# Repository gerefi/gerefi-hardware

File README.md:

# gerefi-hardware

New repo just for gerefi Hardware

See also https://github.com/gerefi/gerefi/tree/master/hardware

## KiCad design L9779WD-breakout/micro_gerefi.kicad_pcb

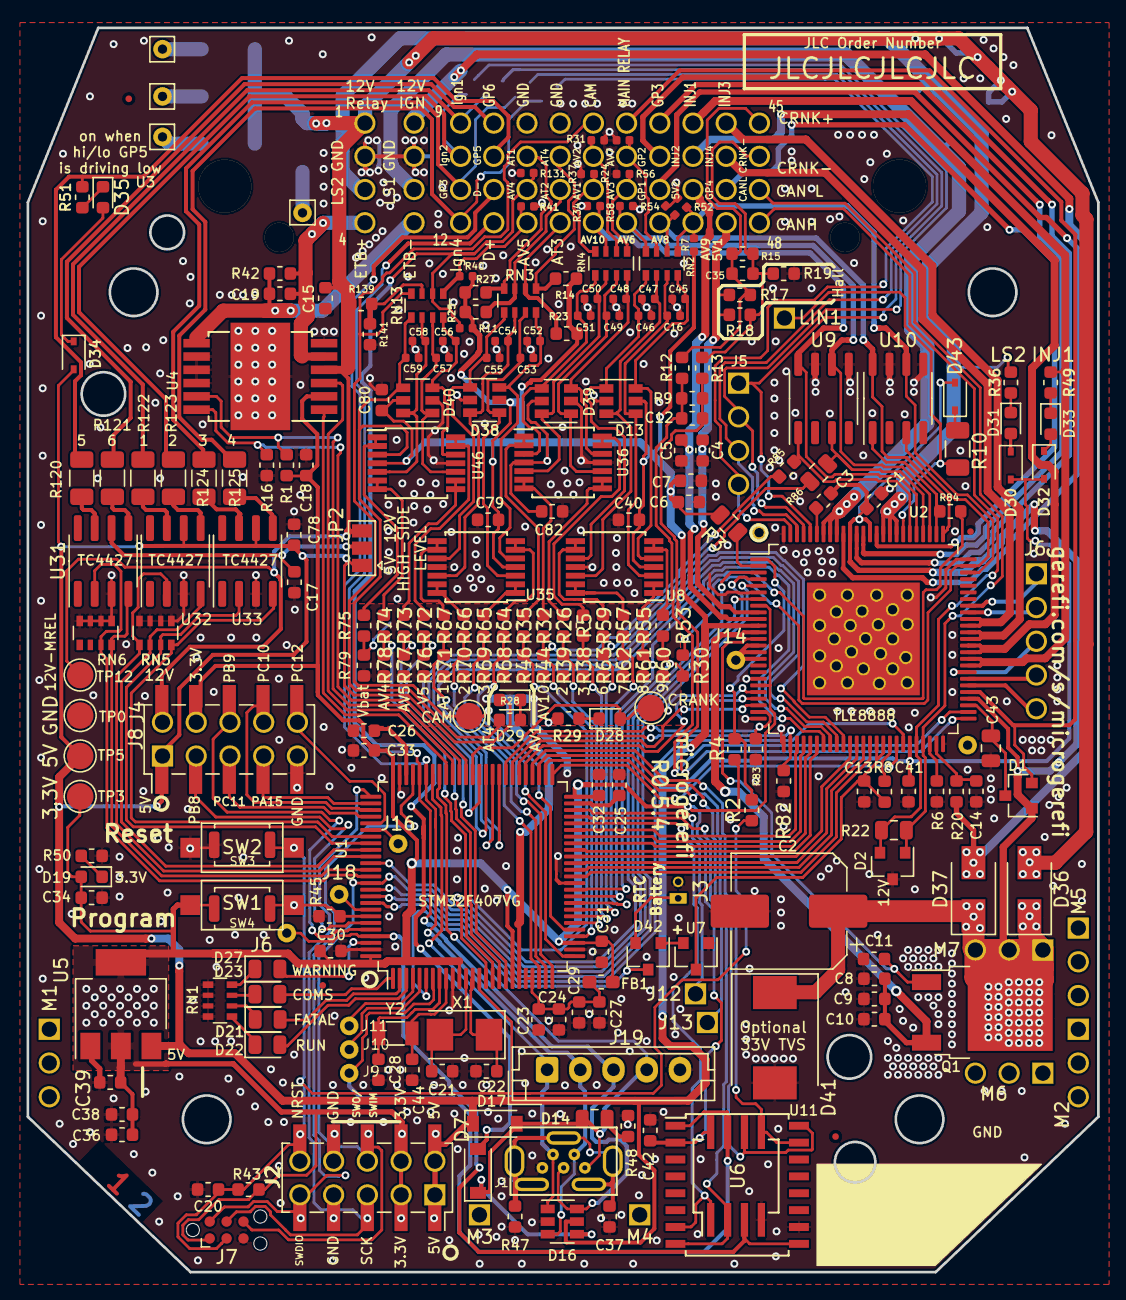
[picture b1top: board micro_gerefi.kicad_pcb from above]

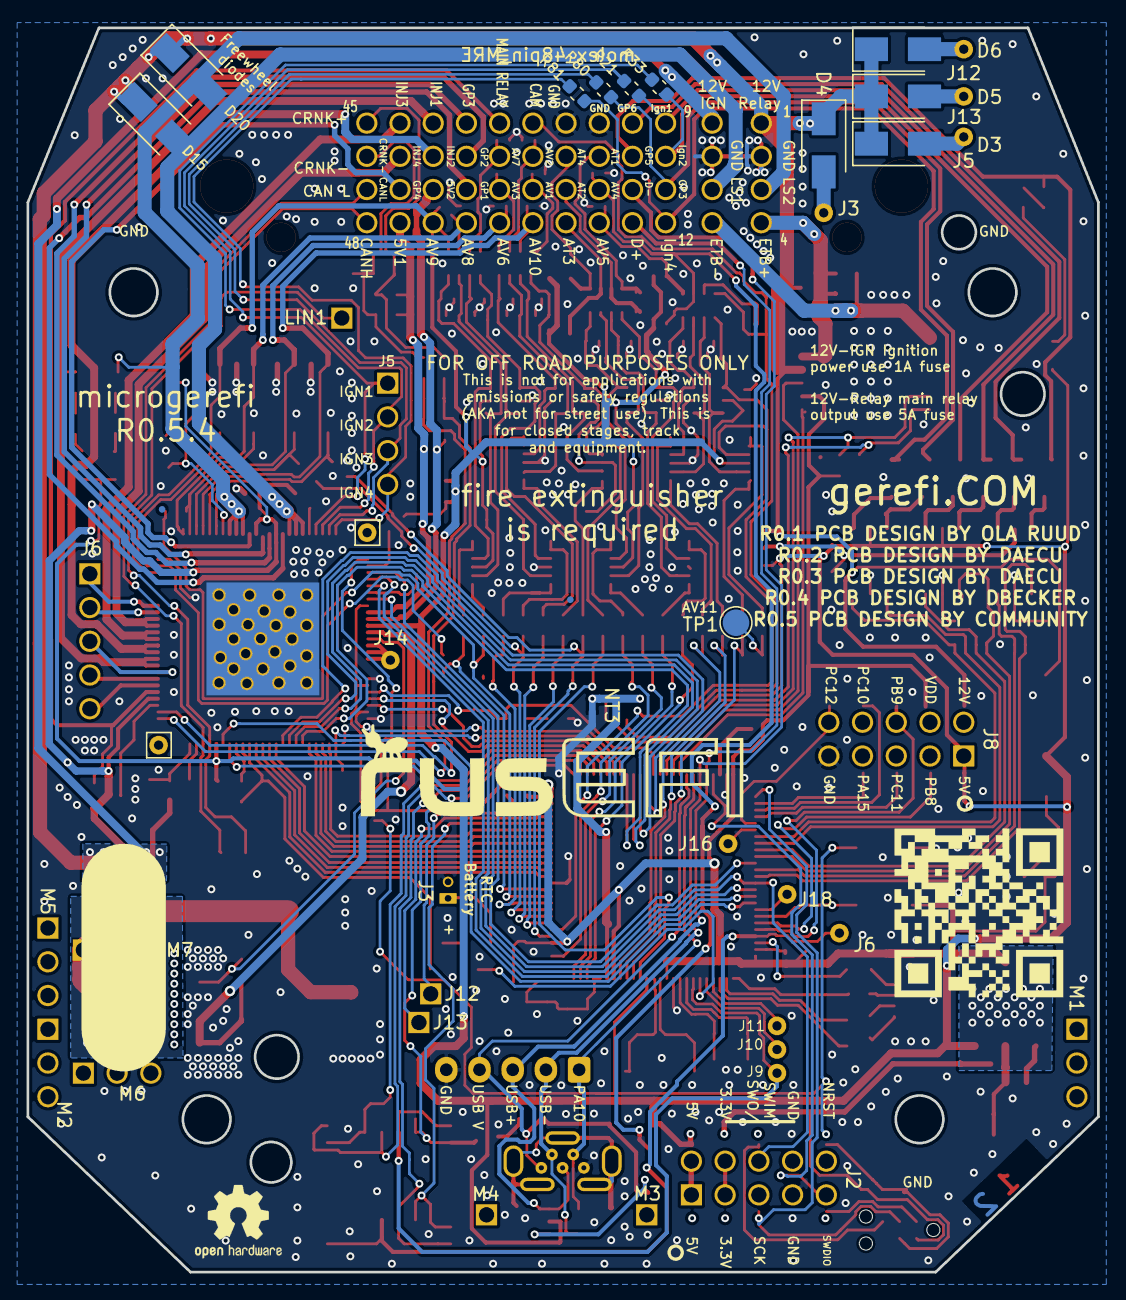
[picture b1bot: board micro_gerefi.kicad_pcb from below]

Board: 2 copper layers, 80.6 x 93.7 mm, 255 parts (19 on the bottom side), 225 nets.

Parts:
C1, C6, C10, C13, C14, C15, C17, C18, C24, C30, C31, C32, C33, C34, C37, C38, C42, C78: 100nF; C_0603_1608Metric
C2: 100UF 50V; CP_Elec_8x10.5
C3, C11: 4.7nF; C_0603_1608Metric
C4, C5: 470nF; C_0603_1608Metric
C7, C8, C9: 10uF; C_0603_1608Metric
C12, C35: 1nF; C_0603_1608Metric
C16, C45, C46, C47, C48, C49, C50, C51, C52, C53, C54, C55, C56, C57, C58, C59: 100nF; C_0402_1005Metric
C19, C20, C29, C40, C79, C80, C82: 10nF; C_0603_1608Metric
C21, C22: 18pF; C_0603_1608Metric
C23, C27, C36: 1uF; C_0603_1608Metric
C25, C26, C41: 2.2uF; C_0603_1608Metric
C28, C44: 6.8pF; C_0603_1608Metric
C39: 22uF; C_0603_1608Metric
C43: 22uF 25V; C_0805_2012Metric
D1, D42: BAV70; SOT-23
D2: PESD1CAN-UX; SOT-23
D3, D4, D5, D6, D15, D20, D36, D37: SS54; D_SMA
D7, D17: B5819W; D_SOD-123
D13, D16, D38, D39, D40: SRV05-4; SOT-23-6
D14: LED-GREEN; C_0805_2012Metric
D19, D28, D29, D31, D33, D35: LED-RED; LED_0603_1608Metric
D21: LED-RED; LED_0805_2012Metric
D22: LED-GREEN; LED_0805_2012Metric
D23: LED-BLUE; LED_0805_2012Metric
D27: LED-YELLOW; LED_0805_2012Metric
D30, D32, D34, D43: 1N4148WS; D_SOD-323
D41: SM15T33C; D_SMC
FB1: FILTER; R_0603_1608Metric_Pad1.05x0.95mm_HandSolder
FID1, FID2, FID3, FID4, FID5, FID6: Fiducial; Fiducial_0.5mm_Mask1mm
G1: Disclaimer; Off_Road_Disclaimer
J1: USB_B_Micro; MINI-USB_RCTP_V-T_B_and_HW-MU-5F-23
J2: Conn_02x05_Odd_Even; PinSocket_2x05_P2.54mm_Vertical_SMD
J3, J5, J12, J13, J15, J17: Conn_01x01; Pin_D0.7mm_L6.5mm_W1.8mm_FlatFork
J4: Conn_02x05_Counter_Clockwise; PinHeader_2x05_P2.54mm_Vertical_SMD
J7: TC2030; Tag-Connect_TC2030-IDC-NL_2x03_P1.27mm_Vertical
J19: Conn_01x06; JST_EH_B5B-EH-A_1x05_P2.50mm_Vertical
JP2: High side voltage 5V 12V; SolderJumper-3_P1.3mm_Open_Pad1.0x1.5mm
LOGO1: DNP; OSHW-Logo2_7.3x6mm_SilkScreen
LOGO3: LOGO; MRE_QR_code
NT1, NT2: Net-Tie_2; Net-Tie_2_8.5mil
NT3: Analog Ground Net Tie; NetTie-2_SMD_Pad0.5mm
Q1: IPD30N06S2L-23; TO-252-2
R1, R4, R6, R12, R13, R16, R38, R39, R43, R44, R45, R46, R60, R61, R62, R63, R68, R69, R70, R71, R76, R77, R78, R79, R141: 10K; R_0603_1608Metric
R2: 0R DNP; R_0603_1608Metric
R3: 10K; R_0805_2012Metric
R5, R26, R32, R35, R53, R55, R57, R59, R64, R65, R66, R67, R72, R73, R74, R75: 6.8K; R_0603_1608Metric
R7, R11, R40: DNP; R_0402_1005Metric
R8, R21, R30, R33, R80, R81, R84, R85: 0R; R_0603_1608Metric
R9, R42, R82, R83: 4.7K; R_0603_1608Metric
R10: 1k; R_1206_3216Metric
R14, R20, R23, R25, R27: 2.7k; R_0603_1608Metric
R15: 15k; R_0603_1608Metric
R17, R18, R19: DNP; R_0603_1608Metric
R22: 120; R_0805_2012Metric
R24, R31, R34, R37, R41, R52, R54, R56, R58, R131: 470K; R_0402_1005Metric
R28, R48: 2.2k; R_0603_1608Metric
R29, R36, R49, R50, R51: 1k; R_0603_1608Metric
R47: 100K; R_0603_1608Metric
R86: 0R; R_0805_2012Metric
R120, R121, R122, R123, R124, R125: 100; R_1206_3216Metric
R139: 39k; R_0603_1608Metric
RN1: 1k; R_Array_Convex_4x0603
RN2, RN3, RN4, RN5, RN6, RN13: 10k; R_Array_Convex_4x0603
SW1, SW2: SW_Push; SW_SPST_CK_RS282G05A3
SW3, SW4: SW_Push; SW_Push_SPST_NO_Alps_SKRK
TP0, TP3: GND; TestPoint_Pad_D2.0mm
TP1, TP2, TP4: TP; TestPoint_Pad_D2.0mm
TP5, TP12: 5V; TestPoint_Pad_D2.0mm
U1: STM32F427VGT6; LQFP-100_14x14mm_P0.5mm
U2: TLE8888QK; LQFP-100_14x14mm_P0.5mm_THERMAL
U3: molex_48pin_MRE; Molex_48_MRE
U4: TLE9201SG; Infineon_PG-DSO-12-11
U5: LM1117-3.3; SOT-223-3_TabPin2
U6: W25Q128JVSIQ; SO-8_5.3x6.2mm_P1.27mm-150+208
U7: XC6206 3.3V; SOT-23
U8, U35, U36, U46: MCP6004; TSSOP-14_4.4x5mm_P0.65mm
U9, U10: VNLD5090; SO-8_3.9x4.9mm_P1.27mm
U11: IS25LP256D-xM; SOIC-16W_7.5x10.3mm_P1.27mm
U31, U32, U33: MIC4427; SOIC-8_3.9x4.9mm_P1.27mm
X1: 8MHz 20pF; Crystal_SMD_5032-2Pin_5.0x3.2mm
Y2: 32768 Hz; Crystal_SMD_3215-2Pin_3.2x1.5mm

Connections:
/5V: C6.1, C7.1, C40.1, C41.1, C78.1, C79.1, C80.1, C82.1, D13.5, D16.5, D17.1, D29.2, D30.2, D32.2, D34.2, D38.5, D39.5, D40.5, J2.1, J2.2, J4.1, JP2.1, R3.2, R7.1, R11.2, R14.2, R23.2, R25.2, R27.2, R40.2, TP5.1, U2.11, U2.45, U3.J201, U3.J202, U3.J801, U5.3, U8.4, U32.6, U33.6, U35.4, U36.4, U46.4
/5V1: C4.1, R17.1, R18.1, U2.9, U3.44
/5V2: C5.1, U2.10, U3.39
/12V_KEY: D37.2, R20.2, U3.5
/12V_MREL: C15.1, D3.1, D4.1, D5.1, D6.1, D15.1, D20.1, D36.2, J4.2, JP2.3, R139.2, TP12.1, U3.1, U3.J802, U4.4
/12V_SAFE: C1.1, C2.1, C3.1, D1.1, D36.1, D37.1, D41.1, D43.2, Q1.2, U2.54, U2.87, U2.90, U3.M71, U3.M72, U3.M73
/ADC/AGND: NT3.2, R38.1, R39.1, R44.1, R46.1, R60.1, R61.1, R62.1, R63.1, R68.1, R69.1, R70.1, R71.1, R76.1, R77.1, R78.1, R79.1, U1.20
/ADC/AV11_MCU: R75.1, R79.2, TP1.1
/AT1: R27.1, RN3.4, U3.18
/AT1_MCU: R67.1, R71.2, U1.23
/AT2: R25.1, RN3.3, U3.23
/AT2_MCU: R66.1, R70.2, U1.24
/AT3: R23.1, RN3.2, U3.24
/AT3_MCU: R65.1, R69.2, U1.25
/AT4: R14.1, RN3.1, U3.22
/AT4_MCU: R64.1, R68.2, U1.26
/AV1: R37.1, RN4.4, U3.27
/AV1_MCU: R35.1, R46.2, U1.15
/AV2: R31.1, RN4.2, U3.26
/AV2_MCU: R26.1, R39.2, U1.31
/AV3: R24.1, RN4.1, U3.31
/AV3_MCU: R5.1, R38.2, U1.32
/AV4: D7.2, R11.1, R131.1, RN13.2, U3.19
/AV4_MCU: R73.1, R77.2, U1.17
/AV5: R40.1, R41.1, RN13.1, U3.20
/AV5_MCU: R72.1, R76.2, U1.18
/AV6: R58.1, RN2.4, U2.78, U3.32, U9.6
/AV6_MCU: R59.1, R63.2, R86.2, U1.33
/AV7: R56.1, RN2.3, U3.30
/AV7_MCU: R57.1, R62.2, U1.34
/AV8: R54.1, RN2.2, U2.76, U3.36, U10.8
/AV8_MCU: R55.1, R61.2, R84.2, U1.35
/AV9: R7.2, R52.1, RN2.1, U2.73, U3.40, U10.6
/AV9_MCU: R30.2, R53.1, R60.2, U1.36
/AV10: R34.1, RN4.3, U2.80, U3.28, U9.8
/AV10_MCU: R32.1, R44.2, R85.2, U1.29
/CAM_MCU: C59.1, D40.4, RN13.5, TP2.1, U1.30, U46.3
/CAM_SENSOR: R28.1, RN13.4, U3.25
/CANH: D2.2, R22.1, U2.46, U3.48
/CANL: D2.1, R22.2, U2.47, U3.47
/CRANK: D28.2, TP4.1, U1.63, U2.21
/CRNK+: C35.1, R12.1, R15.1, R17.2, U3.45
/CRNK-: C35.2, R13.1, R15.2, R18.2, R19.2, U3.46
/CS_TLE: U1.86, U2.3
/E-THROTTLE+: C19.2, R42.2, U3.4, U4.5
/E-THROTTLE-: C19.1, R42.1, U3.8, U4.7
/FlashMemory/CS: U1.46, U6.1, U11.7
/GP1: U2.91, U3.35
/GP2: U2.89, U3.34
/GP3: U2.88, U3.33
/GP4: U2.86, U3.43
/GP5: R51.2, R120.1, U3.14
/GP6: R121.1, U3.13
/H-BRIDGE/DIR: U1.67, U4.1
/H-BRIDGE/DIS: R1.2, U1.65, U4.11
/INJECTOR-1: R49.2, U2.59, U2.60, U3.37
/INJECTOR-2: U2.61, U2.62, U3.38
/INJECTOR-3: U2.63, U2.64, U3.41
/INJECTOR-4: U2.65, U2.66, U3.42
/Ign1: R21.1, R122.1, U3.9
/Ign2: R33.1, R123.1, U3.10
/Ign3: R80.1, R124.1, U3.11
/Ign4: R81.1, R125.1, U3.12
/LINBUS: R10.2, U2.82, U3.LIN1
/LS1: D15.2, U2.92, U2.93, U2.94, U3.7
/LS2: D20.2, R36.2, U2.83, U2.84, U2.85, U3.3
/MAIN_RELAY: D1.2, U2.55, U3.29
/MCU/BOOT0: R45.1, SW1.2, SW4.2, U1.94
/MCU/PA10: D16.1, J1.4, J19.1, U1.69
/MCU/PA13: J2.9, J7.2, U1.72, U3.J209
/MCU/PA14: J2.5, J7.4, U1.76, U3.J205
/MCU/PB2-BOOT1: NT2.2, U1.37
/MCU/PB7: U1.93, U3.J18
/MCU/PB13: U1.52, U6.6, U11.16
/MCU/PB14: U1.53, U6.2, U11.8
/MCU/PB15: U1.54, U6.5, U11.15
/MCU/PC7: R16.1, U1.64, U4.12
/MCU/PC9: U1.66, U4.3
/MCU/PD0: U1.81, U3.J16
/MCU/PE5: U1.4, U3.J11
/MCU/PE6: U1.5, U3.J10
/MCU/USB_VBUS: D7.1, D14.2, D16.4, D17.2, J1.1, J19.4, NT1.2
/MCU/VBAT: D42.1, U7.2
/MCU/VDDA: C23.2, C24.2, C27.2, C29.2, FB1.2, U1.21, U1.22
/MCU/Vrtc: D42.2, U3.J31
/MCU/Vrtcc: D42.3, U1.6
/MCU/shield: C37.1, J1.6, R47.1
/PA15: J4.7, U1.77, U3.J807
/PB8: J4.3, U1.95, U3.J803
/PB9: J4.6, U1.96, U3.J806
/PB10: U1.47, U3.J13
/PB11: U1.48, U3.J12
/PC10: J4.8, U1.78, U3.J808
/PC11: J4.5, U1.79, U3.J805
/PC12: J4.10, U1.80, U3.J810
/PC13: U1.7, U3.J9, U6.7, U11.1
/PD12: U1.59, U2.32
/PD13: U1.60, U2.33
/PD14: U1.61, U2.34
/PD15: U1.62, U2.35
/PE0: U1.97, U3.J6, U6.3, U11.9
/PE1: D27.2, U1.98
/PE2: D23.2, U1.1
/PE3: D21.2, U1.2
/PE4: D22.2, U1.3
/RST: C20.2, J2.10, J7.3, R2.2, R43.2, SW2.1, SW3.1, U1.14, U3.J210
/SCK: J2.6, J7.6, U1.89, U2.7, U3.J206
/SI: U1.91, U2.5
/SO: U1.90, U2.4
/TLE8888-1QK/5V_STBY: C13.1, R8.1, U2.40, U2.41, U7.3
/TLE8888-1QK/BAT_STBY: C43.1, D1.3, U2.53
/TLE8888-1QK/CAN_RX: U1.51, U2.43
/TLE8888-1QK/CAN_TX: U1.92, U2.44
/TLE8888-1QK/IGN_EN: R82.1, U1.57, U2.27
/TLE8888-1QK/IGN_OUT_1: R21.2, U2.96, U3.J51
/TLE8888-1QK/IGN_OUT_2: R33.2, U2.97, U3.J52
/TLE8888-1QK/IGN_OUT_3: R80.2, U2.98, U3.J53
/TLE8888-1QK/IGN_OUT_4: R81.2, U2.99, U3.J54
/TLE8888-1QK/INJ_EN: R83.1, U1.58, U2.24
/TLE8888-1QK/INJ_IN_1: U1.45, U2.28
/TLE8888-1QK/INJ_IN_2: U1.44, U2.29
/TLE8888-1QK/INJ_IN_3: U1.43, U2.30
/TLE8888-1QK/INJ_IN_4: U1.42, U2.31
/TLE8888-1QK/IN_9: U1.41, U2.36
/TLE8888-1QK/IN_10: U1.40, U2.37
/TLE8888-1QK/IN_11: U1.39, U2.38
/TLE8888-1QK/IN_12: U1.38, U2.39
/TLE8888-1QK/KEY: C14.1, R20.1, U2.49
/TLE8888-1QK/LIN_RX: U1.56, U2.23
/TLE8888-1QK/LIN_TX: U1.55, U2.22
/TLE8888-1QK/OUT_7: U2.14, U2.15, U2.16, U3.J14
/TLE8888-1QK/OUT_14: U2.68, U3.J61
/TLE8888-1QK/OUT_15: U2.67, U3.J62
/TLE8888-1QK/OUT_16: U2.58, U3.J63
/TLE8888-1QK/OUT_17: U2.57, U3.J64
/TLE8888-1QK/OUT_18: U2.56, U3.J65
/TLE8888-1QK/RST: R2.1, R4.2, U2.1
/TLE8888-1QK/TLE_MON: R3.1, U2.2
/TLE8888-1QK/V6GATE: C11.1, Q1.1, U2.13
/TLE8888-1QK/V6V: C8.1, C9.1, C10.1, Q1.3, U2.12
/TLE8888-1QK/VR+: C12.1, R9.1, R12.2, U2.52
/TLE8888-1QK/VR-: C12.2, R9.2, R13.2, U2.51
/TLE8888-1QK/WAKE: R6.2, U2.48
/TLE_OUT10_PRE: R30.1, U2.74, U10.3
/TLE_OUT11_PRE: R84.1, U2.77, U10.1
/TLE_OUT12_PRE: R86.1, U2.79, U9.3
/TLE_OUT13_PRE: R85.1, U2.81, U9.1
/USB_D+: D16.6, J1.3, J19.3, U1.71, U3.16
/USB_D-: D16.3, J1.2, J19.2, U1.70, U3.15
/VDD: C18.1, C30.2, C31.2, C32.2, C33.2, C34.2, C36.2, C38.1, C39.2, C42.2, D19.2, FB1.1, J2.3, J2.4, J4.4, J7.1, R1.1, R4.1, R43.1, SW1.1, SW4.1, TP3.1, U1.11, U1.19, U1.28, U1.50, U1.75, U1.100, U2.8, U2.20, U3.J203, U3.J204, U3.J804, U4.2, U5.2, U6.8, U11.2
/Vbat_MCU: R74.1, R78.2, U1.16
/hi-lo/GP5_MCU: RN6.7, U1.88, U31.2
/hi-lo/GP6_MCU: RN6.8, U1.87, U31.4
/hi-lo/Ign1_MCU: RN5.5, U1.85, U32.2
/hi-lo/Ign2_MCU: RN5.6, U1.84, U32.4
/hi-lo/Ign3_MCU: RN5.7, U1.83, U33.2
/hi-lo/Ign4_MCU: RN5.8, U1.82, U33.4
GND: C1.2, C2.2, C4.2, C5.2, C6.2, C7.2, C8.2, C9.2, C10.2, C11.2, C13.2, C14.2, C15.2, C16.2, C17.2, C18.2, C20.1, C21.2, C22.2, C23.1, C24.1, C25.2, C26.2, C27.1, C28.2, C29.1, C30.1, C31.1, C32.1, C33.1, C34.1, C36.1, C37.2, C38.2, C39.1, C40.2, C41.2, C42.1, C43.2, C44.1, C45.2, C46.2, C47.2, C48.2, C49.2, C50.2, C51.2, C52.2, C53.2, C54.2, C55.2, C56.2, C57.2, C58.2, C59.2, C78.2, C79.2, C80.2, C82.2, D2.3, D13.2, D16.2, D38.2, D39.2, D40.2, D41.2, J1.5, J2.7, J2.8, J4.9, J7.5, J19.5, NT2.1, NT3.1, R6.1, R16.2, R19.1, R24.2, R29.2, R31.2, R34.2, R37.2, R41.2, R45.2, R47.2, R48.1, R50.1, R52.2, R54.2, R56.2, R58.2, R82.2, R83.2, R131.2, R141.2, RN1.5, RN1.6, RN1.7, RN1.8, RN5.1, RN5.2, RN5.3, RN5.4, RN6.1, RN6.2, RN6.3, RN6.4, SW2.2, SW3.2, TP0.1, U1.10, U1.27, U1.74, U1.99, U2.6, U2.19, U2.25, U2.26, U2.50, U2.75, U2.100, U2.101, U3.2, U3.6, U3.17, U3.21, U3.J32, U3.J207, U3.J208, U3.J809, U4.6, U4.8, U4.9, U4.10, U4.13, U5.1, U6.4, U7.1, U8.11, U9.5, U9.7, U10.5, U10.7, U11.10, U31.3, U32.3, U33.3, U35.11, U36.11, U46.11
unnamed: C3.2, U2.95
unnamed: C16.1, D13.6, RN2.8, U8.5
unnamed: C17.1, JP2.2, U31.6
unnamed: C21.1, U1.12, X1.2
unnamed: C22.1, U1.13, X1.1
unnamed: C25.1, U1.49
unnamed: C26.1, U1.73
unnamed: C28.1, U1.8, Y2.1
unnamed: C44.2, U1.9, Y2.2
unnamed: C45.1, D13.4, RN2.7, U8.3
unnamed: C46.1, D13.3, RN2.6, U8.12
unnamed: C47.1, D13.1, RN2.5, U8.10
unnamed: C48.1, D39.3, RN4.8, U36.12
unnamed: C49.1, D39.1, RN4.7, U36.10
unnamed: C50.1, D39.6, RN4.6, U36.5
unnamed: C51.1, D39.4, RN4.5, U36.3
unnamed: C52.1, D38.6, RN3.8, U35.5
unnamed: C53.1, D38.4, RN3.7, U35.3
unnamed: C54.1, D38.3, RN3.6, U35.12
unnamed: C55.1, D38.1, RN3.5, U35.10
unnamed: C56.1, D40.3, RN13.8, U46.12
unnamed: C57.1, D40.1, RN13.7, U46.10
unnamed: C58.1, D40.6, RN13.6, U46.5
unnamed: D3.2, J5.1
unnamed: D4.2, J3.1
unnamed: D5.2, J13.1
unnamed: D6.2, J12.1
unnamed: D14.1, R48.2
unnamed: D19.1, R50.2
unnamed: D21.1, RN1.2
unnamed: D22.1, RN1.1
unnamed: D23.1, RN1.3
unnamed: D27.1, RN1.4
unnamed: D28.1, R29.1
unnamed: D29.1, R28.2
unnamed: D30.1, D31.2
unnamed: D31.1, R36.1
unnamed: D32.1, D33.2
unnamed: D33.1, R49.1
unnamed: D34.1, D35.2
unnamed: D35.1, R51.1
unnamed: D43.1, R10.1
unnamed: NT1.1, U1.68
unnamed: R5.2, U36.13, U36.14
unnamed: R8.2, U2.42
unnamed: R26.2, U36.8, U36.9
unnamed: R32.2, U36.6, U36.7
unnamed: R35.2, U36.1, U36.2
unnamed: R53.2, U8.6, U8.7
unnamed: R55.2, U8.1, U8.2
unnamed: R57.2, U8.13, U8.14
unnamed: R59.2, U8.8, U8.9
unnamed: R64.2, U35.6, U35.7
unnamed: R65.2, U35.1, U35.2
unnamed: R66.2, U35.13, U35.14
unnamed: R67.2, U35.8, U35.9
unnamed: R72.2, U46.13, U46.14
unnamed: R73.2, U46.8, U46.9
unnamed: R74.2, U46.6, U46.7
unnamed: R75.2, U46.1, U46.2
unnamed: R120.2, U31.7
unnamed: R121.2, U31.5
unnamed: R122.2, U32.7
unnamed: R123.2, U32.5
unnamed: R124.2, U33.7
unnamed: R125.2, U33.5
unnamed: R139.1, R141.1, RN13.3

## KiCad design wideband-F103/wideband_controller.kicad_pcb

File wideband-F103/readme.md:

Self-contained LSU wideband supporting both STM32F103 and GD32F103

See https://github.com/mck1117/wideband

115200 baud

[.ini](https://github.com/dron0gus/wideband/blob/master/firmware/ini/gerefi_wb_f1.ini)

# Changelog

# rev 4

* Iteration of rev 3 with fixed PCB dimensions
* Improved RC filter on digital input lines
* Pinout changes https://github.com/gerefi/gerefi-hardware/pull/153

# rev 3

* New board
* Microcontroller replaced
* Added four digital inputs
* Added bluetooth module
* Now LQFP-64
* In-action demo https://youtu.be/ZzZXdSdfkbs

# rev 2

* Firmware binaries https://github.com/gerefi/gerefi-hardware/releases/tag/20220904
* Silkscreen improvements on back side
* 2x7 debug port moved to top side
* VBatt sense added
* Still LQFP-48

# rev 1

* Works with LQFP-48 STM32 and GD32
* PWM required HW hacks

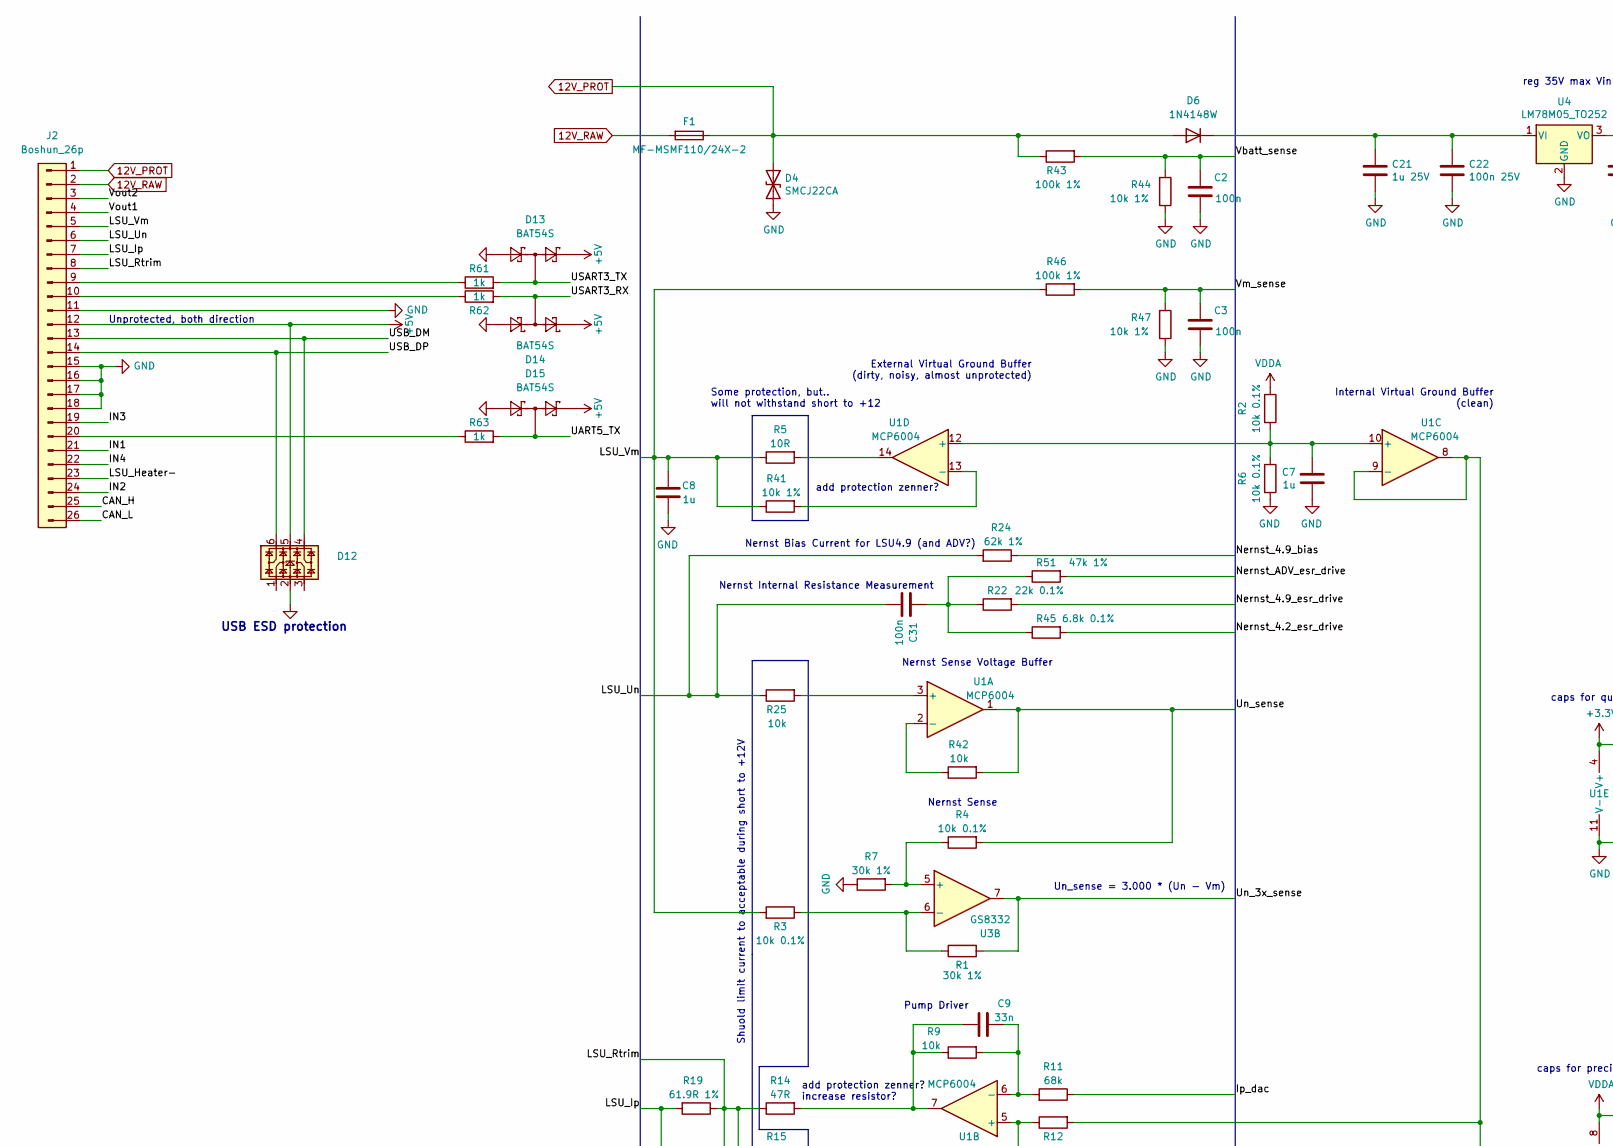
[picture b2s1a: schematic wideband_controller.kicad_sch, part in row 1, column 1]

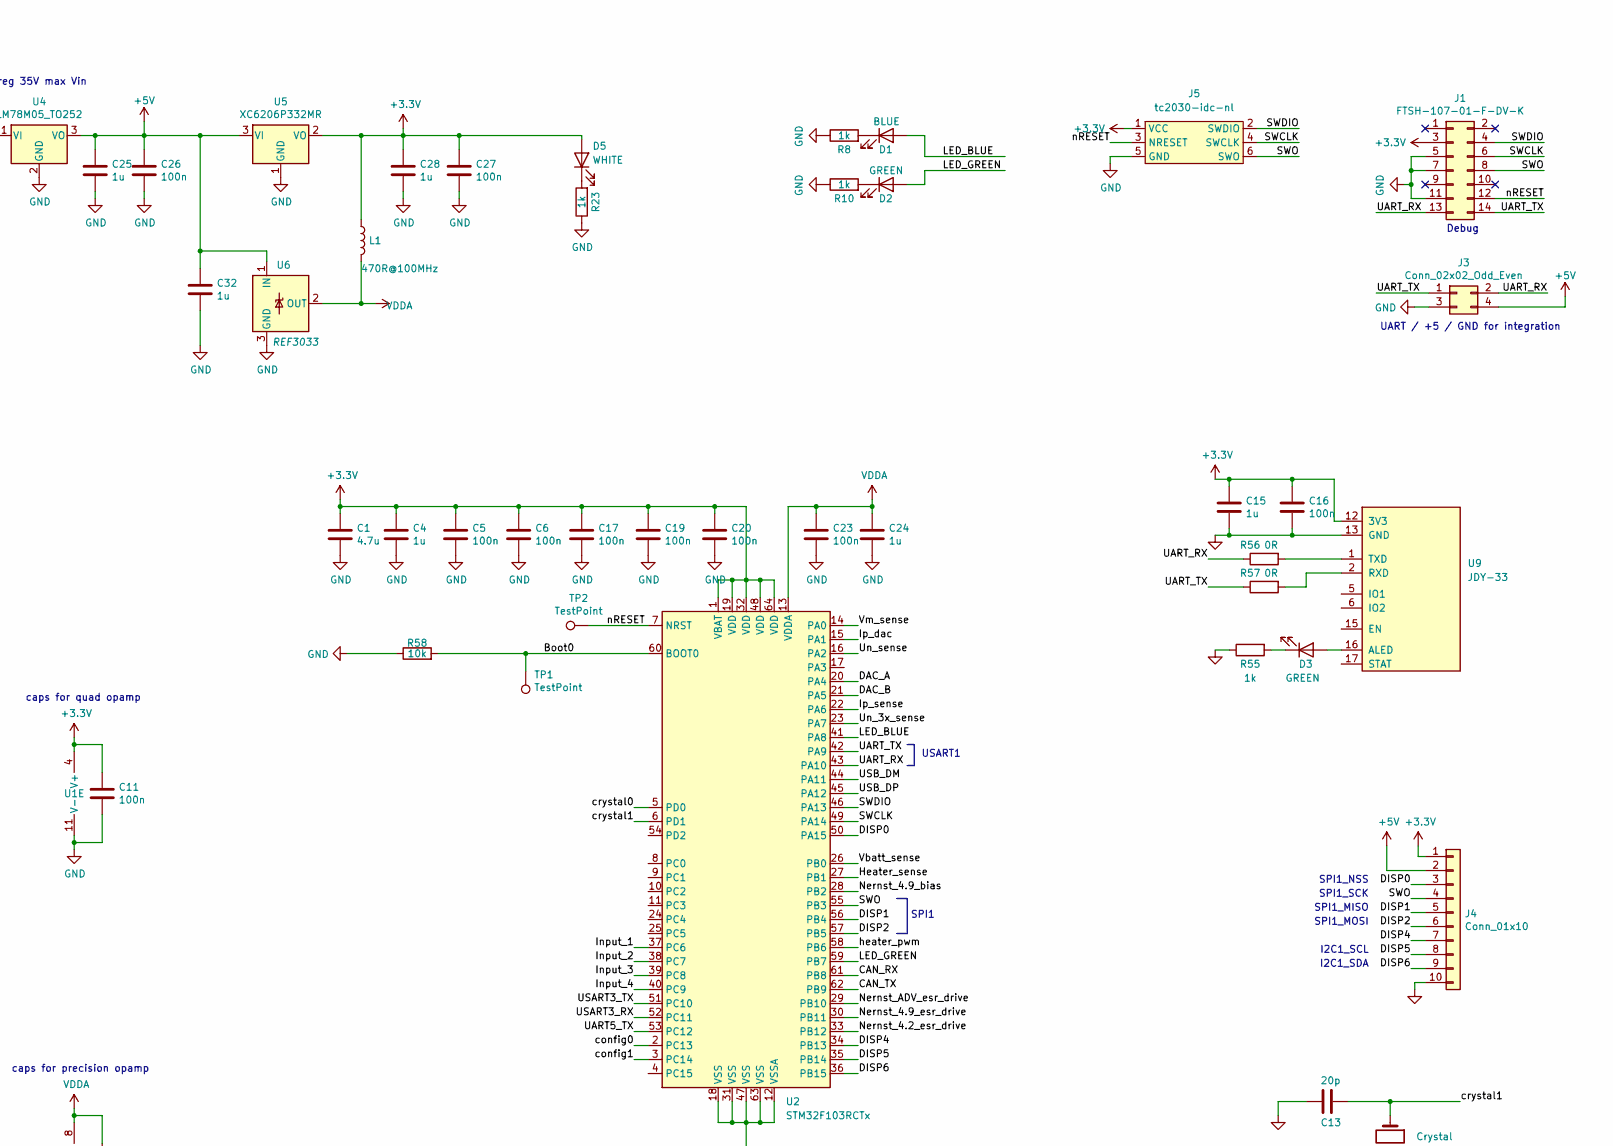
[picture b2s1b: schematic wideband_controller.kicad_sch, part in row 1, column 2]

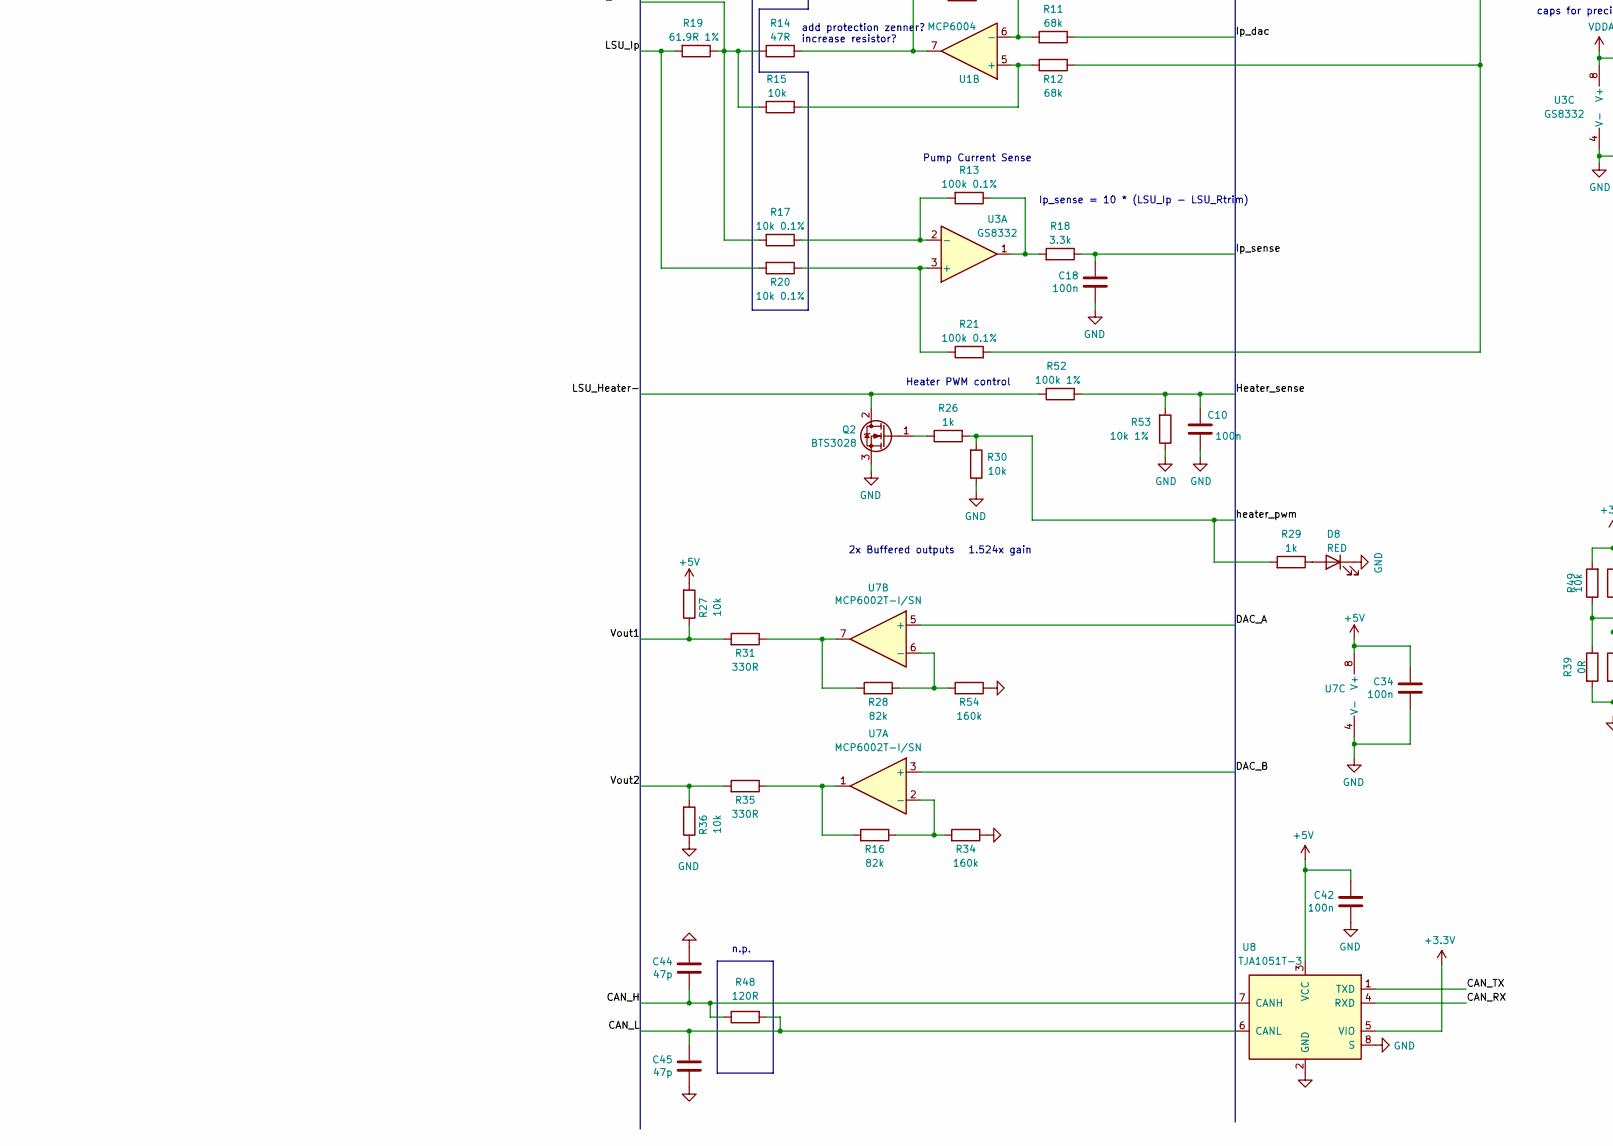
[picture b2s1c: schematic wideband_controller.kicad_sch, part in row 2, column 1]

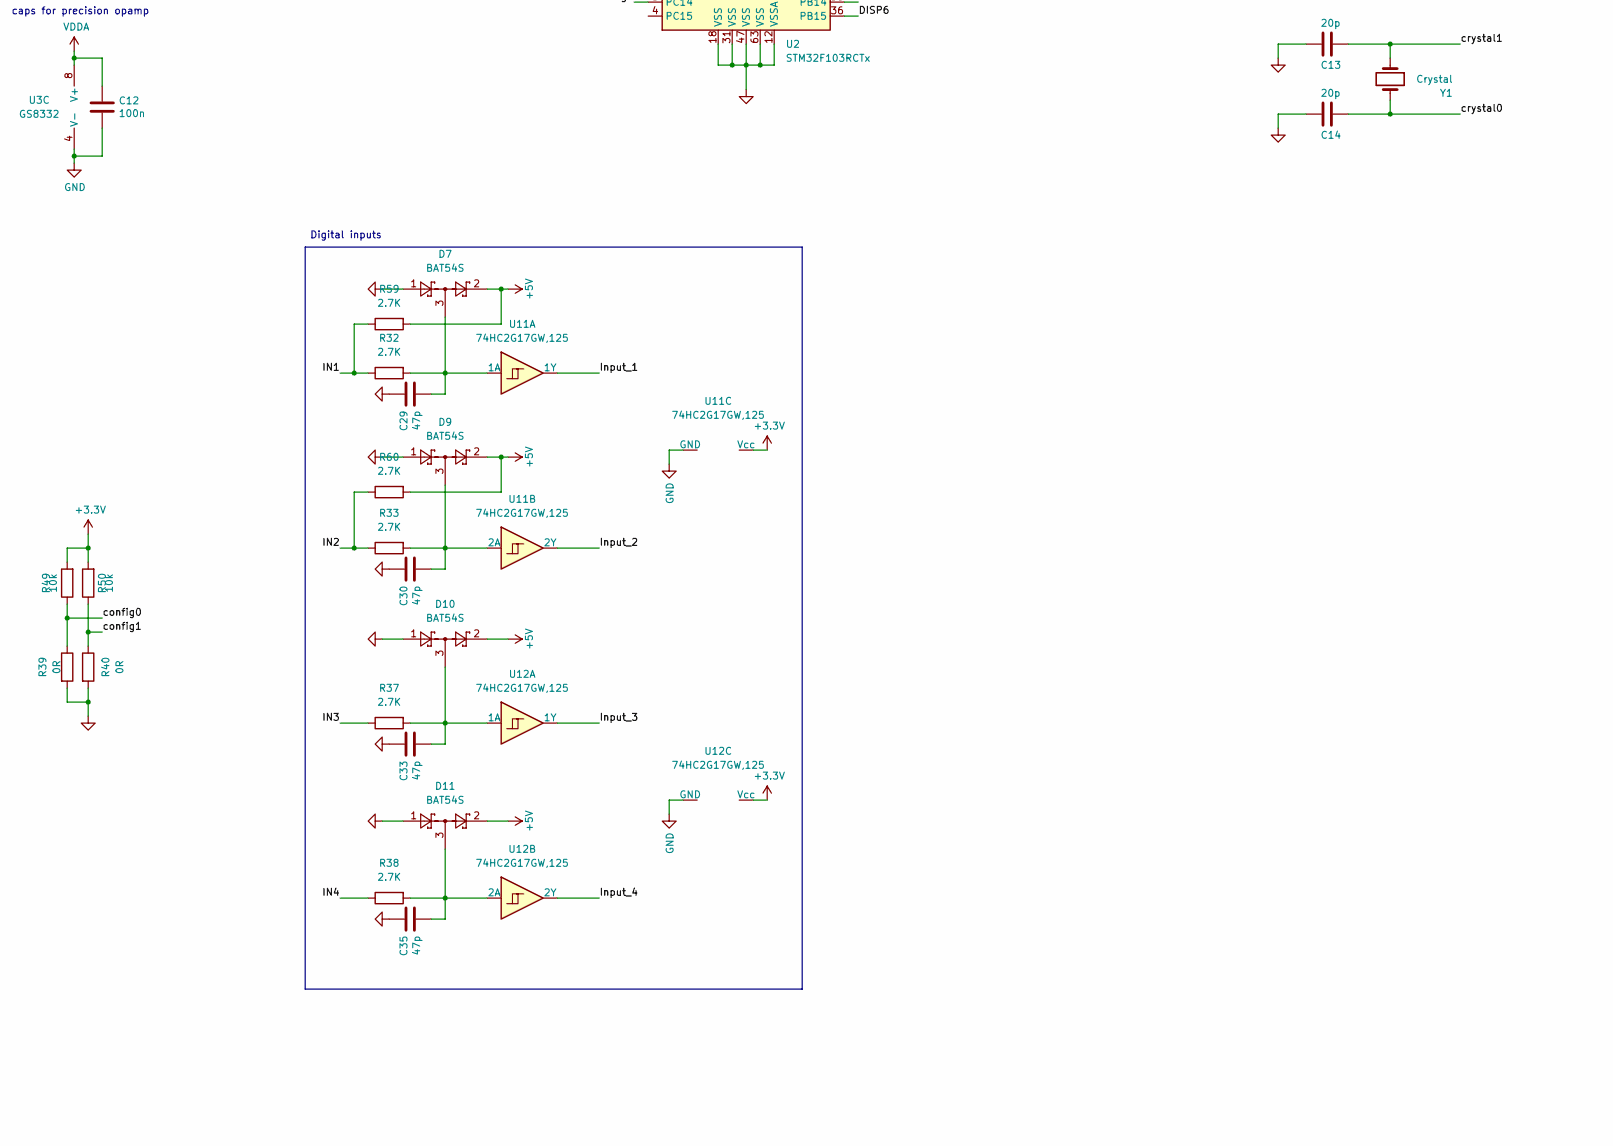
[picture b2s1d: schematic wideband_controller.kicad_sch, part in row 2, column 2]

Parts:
C1: 4.7u; C_0402_1005Metric; LCSC C23733
C2, C3, C5, C6, C10, C11, C12, C16, C17, C18, C19, C20, C23, C26, C27, C31, C34, C42: 100n; C_0402_1005Metric; LCSC C1525
C4, C7, C8, C15, C24, C25, C28, C32: 1u; C_0402_1005Metric; LCSC C52923
C9: 33n; C_0402_1005Metric; LCSC C1585
C13, C14: 20p; C_0402_1005Metric; LCSC C52923
C21: 1u 25V; C_0603_1608Metric; LCSC C15849
C22: 100n 25V; C_0603_1608Metric; LCSC C14663
C29, C30, C33, C35, C44, C45: 47p; C_0402_1005Metric; LCSC C1567
D1: BLUE; LED_0603_1608Metric; LCSC C72041
D2, D3: GREEN; LED_0603_1608Metric; LCSC C72043
D4: SMCJ22CA; D_SMC; LCSC C310038
D5: WHITE; LED_0603_1608Metric; LCSC C2290
D6: 1N4148W; D_SOD-123; LCSC C81598
D7, D9, D10, D11, D13, D14, D15: BAT54S; SOT-23; LCSC C2903789
D8: RED; LED_0603_1608Metric; LCSC C2286
D12: TSOP-6; LCSC C85364
F1: MF-MSMF110/24X-2; Fuse_1812_4532Metric_Pad1.30x3.40mm_HandSolder; JLCPCB C210835
J1: FTSH-107-01-F-DV-K; PinHeader_2x07_P1.27mm_Vertical_SMD
J2: Boshun_26p; Boshun_26pin
J3: Conn_02x02_Odd_Even; PinHeader_2x02_P2.54mm_Vertical
J4: Conn_01x10; PinHeader_1x10_P2.54mm_Vertical
J5: tc2030-idc-nl
L1: 470R@100MHz; L_0603_1608Metric; LCSC C97853
Q2: BTS3028; TO-252-2; LCSC C112639
R1, R7: 30k 1%; R_0603_1608Metric; LCSC C22984
R2, R3, R4, R6, R17, R20: 10k 0.1%; R_0603_1608Metric; LCSC C309083
R5: 10R; R_1206_3216Metric; LCSC C17903
R8, R10, R23, R26, R29, R55, R61, R62, R63: 1k; R_0402_1005Metric; LCSC C11702
R9, R15, R25, R27, R36, R42, R49, R50, R58: 10k; R_0402_1005Metric; LCSC C25744
R11, R12: 68k; R_0402_1005Metric; LCSC C36871
R13, R21: 100k 0.1%; R_0603_1608Metric; LCSC C122538
R14: 47R; R_0603_1608Metric; LCSC C328363
R16, R28: 82k; R_0603_1608Metric; LCSC C23254
R18: 3.3k; R_0402_1005Metric; LCSC C25890
R19: 61.9R 1%; R_0805_2012Metric; LCSC C322537
R22: 22k 0.1%; R_0603_1608Metric; LCSC C133163
R24: 62k 1%; R_0603_1608Metric; LCSC C23221
R30: 10k; R_0402_1005Metric; LCSC C11702
R31, R35: 330R; R_0603_1608Metric; LCSC C23138
R32, R33, R37, R38, R59, R60: 2.7K; R_1206_3216Metric; JLCPCB C17950
R34, R54: 160k; R_0603_1608Metric; LCSC C22813
R39, R40: 0R; R_0402_1005Metric; LCSC C325377
R41, R44, R47, R53: 10k 1%; R_0402_1005Metric; LCSC C25744
R43, R46, R52: 100k 1%; R_0402_1005Metric; LCSC C25741
R45: 6.8k 0.1%; R_0603_1608Metric; LCSC C705876
R48: 120R; R_1206_3216Metric; LCSC C176250
R51: 47k 1%; R_0603_1608Metric; LCSC C25819
R56, R57: 0R; R_0402_1005Metric; JLCPCB C17168
TP1, TP2: TestPoint; PinHeader_1x01_P2.54mm_Vertical
U1: MCP6004; TSSOP-14_4.4x5mm_P0.65mm; LCSC C50282
U2: STM32F103RCTx; LQFP-64_10x10mm_P0.5mm
U3: GS8332; TSSOP-8_3x3mm_P0.65mm; LCSC C157714
U4: LM78M05_TO252; TO-252-2; LCSC C58069
U5: XC6206P332MR; SOT-23; LCSC C5446
U6: REF3033; SOT-23; LCSC C36658
U7: MCP6002T-I/SN; SO-8_3.9x4.9mm_P1.27mm; LCSC C7377
U8: TJA1051T-3; SOIC-8_3.9x4.9mm_P1.27mm; LCSC C38695
U9: JDY-33; PARTREV v1.0
U11, U12: 74HC2G17GW,125; SOT-23-6; LCSC C94189
Y1: Crystal; Crystal_SMD_HC49-SD; JLCPCB C108703

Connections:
12V_PROT: D4.1 (A1), D6.2 (A), F1.1, J2.1, R43.1
12V_RAW: F1.2, J2.2
+3V3: C1.1, C4.1, C5.1, C6.1, C11.1, C15.1, C16.1, C17.1, C19.1, C20.1, C27.1, C28.1, D5.2 (A), J1.3, J4.1, J5.1 (VCC), L1.1, R49.2, R50.2, U1.4 (V+), U2.1 (VBAT), U2.19 (VDD), U2.32 (VDD), U2.48 (VDD), U2.64 (VDD), U5.2 (VO), U8.5 (VIO), U9.12 (3V3), U11.5 (Vcc), U12.5 (Vcc)
+5V: C25.1, C26.1, C32.1, C34.1, C42.1, D7.2, D9.2, D10.2, D11.2, D12.5, D13.2, D14.2, D15.2, J2.12, J3.4, J4.2, R27.2, R59.2, R60.2, U4.3 (VO), U5.3 (VI), U6.1 (IN), U7.8 (V+), U8.3 (VCC)
/Boot0: R58.2, TP1.1, U2.60 (BOOT0)
/CAN_H: C44.2, J2.25, R48.1, U8.7 (CANH)
/CAN_L: C45.1, J2.26, R48.2, U8.6 (CANL)
/CAN_RX: U2.61 (PB8), U8.4 (RXD)
/CAN_TX: U2.62 (PB9), U8.1 (TXD)
/DAC_A: U2.20 (PA4), U7.5 (+)
/DAC_B: U2.21 (PA5), U7.3 (+)
/DISP0: J4.3, U2.50 (PA15)
/DISP1: J4.5, U2.56 (PB4)
/DISP2: J4.6, U2.57 (PB5)
/DISP4: J4.7, U2.34 (PB13)
/DISP5: J4.8, U2.35 (PB14)
/DISP6: J4.9, U2.36 (PB15)
/Heater_sense: C10.1, R52.2, R53.2, U2.27 (PB1)
/IN1: J2.21, R32.1, R59.1
/IN2: J2.24, R33.1, R60.1
/IN3: J2.19, R37.1
/IN4: J2.22, R38.1
/Input_1: U2.37 (PC6), U11.6 (1Y)
/Input_2: U2.38 (PC7), U11.4 (2Y)
/Input_3: U2.39 (PC8), U12.6 (1Y)
/Input_4: U2.40 (PC9), U12.4 (2Y)
/Ip_dac: R11.1, U2.15 (PA1)
/Ip_sense: C18.1, R18.1, U2.22 (PA6)
/LED_BLUE: D1.2 (A), U2.41 (PA8)
/LED_GREEN: D2.2 (A), U2.59 (PB7)
/LSU_Heater-: J2.23, Q2.2 (D), R52.1
/LSU_Ip: J2.7, R19.2, R20.2
/LSU_Rtrim: J2.8, R14.1, R15.1, R17.2, R19.1
/LSU_Un: C31.1, J2.6, R24.2, R25.1
/LSU_Vm: C8.1, J2.5, R3.2, R5.1, R41.1, R46.1
/Nernst_4.2_esr_drive: R45.2, U2.33 (PB12)
/Nernst_4.9_bias: R24.1, U2.28 (PB2)
/Nernst_4.9_esr_drive: R22.2, U2.30 (PB11)
/Nernst_ADV_esr_drive: R51.2, U2.29 (PB10)
/SWCLK: J1.6, J5.4 (SWCLK), U2.49 (PA14)
/SWDIO: J1.4, J5.2 (SWDIO), U2.46 (PA13)
/SWO: J1.8, J4.4, J5.6 (SWO), U2.55 (PB3)
/UART5_TX: D15.3, R63.2, U2.53 (PC12)
/UART_RX: J1.13, J3.2, R56.1, U2.43 (PA10)
/UART_TX: J1.14, J3.1, R57.1, U2.42 (PA9)
/USART3_RX: D14.3, R62.2, U2.52 (PC11)
/USART3_TX: D13.3, R61.2, U2.51 (PC10)
/USB_DM: D12.4, J2.13, U2.44 (PA11)
/USB_DP: D12.6, J2.14, U2.45 (PA12)
/Un_3x_sense: R1.2, U2.23 (PA7), U3.7
/Un_sense: R4.2, R42.2, U1.1, U2.16 (PA2)
/Vbatt_sense: C2.1, R43.2, R44.2, U2.26 (PB0)
/Vm_sense: C3.1, R46.2, R47.2, U2.14 (PA0)
/Vout1: J2.4, R27.1, R31.2
/Vout2: J2.3, R35.2, R36.2
/config0: R39.1, R49.1, U2.2 (PC13)
/config1: R40.1, R50.1, U2.3 (PC14)
/crystal0: C14.1, U2.5 (PD0), Y1.2
/crystal1: C13.1, U2.6 (PD1), Y1.1
/heater_pwm: R26.2, R29.2, R30.2, U2.58 (PB6)
/nRESET: J1.12, J5.3 (NRESET), TP2.1, U2.7 (NRST)
GND: C1.2, C2.2, C3.2, C4.2, C5.2, C6.2, C7.2, C8.2, C10.2, C11.2, C12.2, C13.2, C14.2, C15.2, C16.2, C17.2, C18.2, C19.2, C20.2, C21.2, C22.2, C23.2, C24.2, C25.2, C26.2, C27.2, C28.2, C29.1, C30.1, C32.2, C33.1, C34.2, C35.1, C42.2, C44.1, C45.2, D4.2 (A2), D7.1, D8.1 (K), D9.1, D10.1, D11.1, D12.2, D13.1, D14.1, D15.1, J1.5, J1.7, J1.11, J2.11, J2.15, J2.16, J2.17, J2.18, J3.3, J4.10, J5.5 (GND), Q2.3 (S), R6.2, R7.1, R8.1, R10.1, R23.1, R30.1, R34.1, R36.1, R39.2, R40.2, R44.1, R47.1, R53.1, R54.1, R55.1, R58.1, U1.11 (V-), U2.12 (VSSA), U2.18 (VSS), U2.31 (VSS), U2.47 (VSS), U2.63 (VSS), U3.4 (V-), U4.2 (GND), U5.1 (GND), U6.3 (GND), U7.4 (V-), U8.2 (GND), U8.8 (S), U9.13 (GND), U11.2 (GND), U12.2 (GND)
unnamed: C7.1, R2.2, R6.1, U1.10 (+), U1.12 (+)
unnamed: C9.1, R9.1, R14.2, U1.7
unnamed: C9.2, R9.2, R11.2, U1.6 (-)
unnamed: C21.1, C22.1, D6.1 (K), U4.1 (VI)
unnamed: C29.2, D7.3, R32.2, U11.1 (1A)
unnamed: C30.2, D9.3, R33.2, U11.3 (2A)
unnamed: C31.2, R22.1, R45.1, R51.1
unnamed: C33.2, D10.3, R37.2, U12.1 (1A)
unnamed: C35.2, D11.3, R38.2, U12.3 (2A)
unnamed: D1.1 (K), R8.2
unnamed: D2.1 (K), R10.2
unnamed: D3.1 (K), R55.2
unnamed: D3.2 (A), U9.16 (ALED)
unnamed: D5.1 (K), R23.2
unnamed: D8.2 (A), R29.1
unnamed: J2.9, R61.1
unnamed: J2.10, R62.1
unnamed: J2.20, R63.1
unnamed: Q2.1 (G), R26.1
unnamed: R1.1, R3.1, U3.6 (-)
unnamed: R4.1, R7.2, U3.5 (+)
unnamed: R5.2, U1.14
unnamed: R12.1, R15.2, U1.5 (+)
unnamed: R12.2, R21.2, U1.8, U1.9 (-)
unnamed: R13.1, R18.2, U3.1
unnamed: R13.2, R17.1, U3.2 (-)
unnamed: R16.1, R34.2, U7.2 (-)
unnamed: R16.2, R35.1, U7.1
unnamed: R20.1, R21.1, U3.3 (+)
unnamed: R25.2, U1.3 (+)
unnamed: R28.1, R54.2, U7.6 (-)
unnamed: R28.2, R31.1, U7.7
unnamed: R41.2, U1.13 (-)
unnamed: R42.1, U1.2 (-)
unnamed: R56.2, U9.1 (TXD)
unnamed: R57.2, U9.2 (RXD)
VDDA: C12.1, C23.1, C24.1, L1.2, R2.1, U2.13 (VDDA), U3.8 (V+), U6.2 (OUT)

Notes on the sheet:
Nernst Internal Resistance Measurement
Pump Current Sense
Ip_sense = 10 * (LSU_Ip - LSU_Rtrim)
reg 35V max Vin
SPI1_MOSI
Unprotected, both direction
Shuold limit current to acceptable during short to +12V
Internal Virtual Ground Buffer (clean)
I2C1_SCL
External Virtual Ground Buffer (dirty, noisy, almost unprotected)
Pump Driver
USB ESD protection
Nernst Sense
Un_sense = 3.000 * (Un - Vm)
Nernst Bias Current for LSU4.9 (and ADV?)
Digital inputs
Debug
n.p.
add protection zenner? increase resistor?
2x Buffered outputs
caps for precision opamp
Some protection, but.. will not withstand short to +12
SPI1
1.524x gain
SPI1_SCK
Nernst Sense Voltage Buffer
add protection zenner?
SPI1_NSS
caps for quad opamp
Heater PWM control
USART1
I2C1_SDA
UART / +5 / GND for integration
SPI1_MISO
